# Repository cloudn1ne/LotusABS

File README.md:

# LotusABS

<table border=0>
<tr>
<td></td>
<td colspan=2></td>
</tr><tr>
<td></td>
<td></td>
<td></td>
</tr>
</table>

## What can you do with it ?

The software part is a pretty minimum implementation of the KWP2000 via K-LINE as used by the EBC430 EBC.
The supported Service IDs are:

Function | Usage
-------- | -----
StartCommunication | start a KWP2000 session
ReadECUIdentification | ECU details, nothing new here - same as listed in the Lotus Service Manual
ReadDataByLocalId | battery voltage, wheel speeds (not implemented, because my car is not moving atm)
ReadDiagnosticTroubleCodeByStatus | read DTC codes and status reasons
ClearDiagnosticInformationService | clear and DTCs
InputOutputControlByLocalId | control the valves, pump, relay

So with that you can establish communication with the ECU, get software/hardware versions, battery voltage (wheels speeds later on), read and clear DTCs, and most importantly
control the valves, pump and valve relay to aid with bleeding.

## How can i use it ?

You need to solder up the little ESP8266 based adapter (or put it on breadboard if you are adventurous. A proven PCB design and circuit is included in the ./pcb folder.
It was made with KiCAD (www.kicad.org)

## Whats the difference to existing KLINE/OBD Tools ?

Not much - i didnt have one, so i had to roll my own - the most notible difference is that the KLINE line has to be on PIN #12 of the OBD connector (usualy it would be Pin #7)
And you wont have a GUI to control stuff.

## Software
The project is based on PLATFORM.IO - download VS Code and install platform IO (https://platformio.org/) 

## Hardware
see KiCAD

### As usual that tool comes with no warranty, it might blow up your airbags (same KLINE) or set your car on fire. Good luck ;-)

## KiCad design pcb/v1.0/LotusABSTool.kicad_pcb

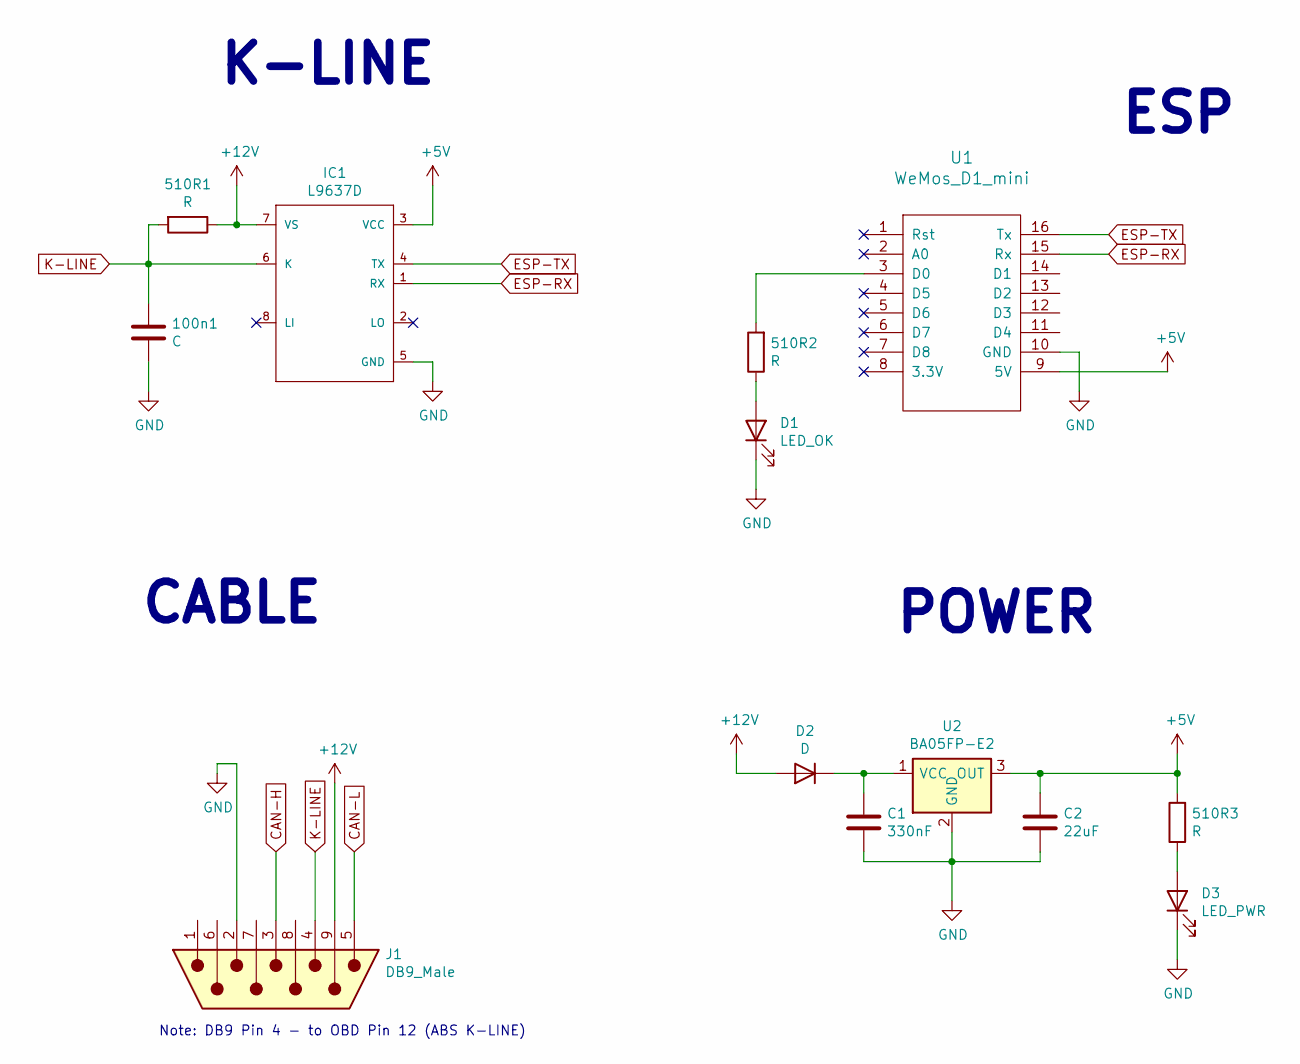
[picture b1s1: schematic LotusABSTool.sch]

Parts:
100n1: C; C_0805_2012Metric_Pad1.18x1.45mm_HandSolder
510R1, 510R2, 510R3: R; R_0805_2012Metric_Pad1.20x1.40mm_HandSolder
C1: 330nF; C_0805_2012Metric_Pad1.18x1.45mm_HandSolder
C2: 22uF; CP_Elec_10x10.5
D1: LED_OK; LED_0805_2012Metric_Pad1.15x1.40mm_HandSolder
D2: D; D_SMA-SMB_Universal_Handsoldering
D3: LED_PWR; LED_0805_2012Metric_Pad1.15x1.40mm_HandSolder
IC1: L9637D; SO-8_3.9x4.9mm_P1.27mm
J1: DB9_Male; DSUB-9_Male_Vertical_P2.77x2.84mm_MountingHoles
U1: WeMos_D1_mini; wemos-d1-mini-with-pin-header
U2: BA05FP-E2; TO-252-2

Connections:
+5V: 510R3.2, C2.1, IC1.3 (VCC), U1.9 (5V), U2.3 (OUT)
+12V: 510R1.1, D2.2 (A), IC1.7 (VS), J1.9
CAN-H: J1.3
CAN-L: J1.5
ESP-RX: IC1.1 (RX), U1.15 (Rx)
ESP-TX: IC1.4 (TX), U1.16 (Tx)
GND: 100n1.2, C1.2, C2.2, D1.1 (K), D3.1 (K), IC1.5 (GND), J1.2, U1.10 (GND), U2.2 (GND)
K-LINE: 100n1.1, 510R1.2, IC1.6 (K), J1.4
unnamed: 510R2.1, D1.2 (A)
unnamed: 510R2.2, U1.3 (D0)
unnamed: 510R3.1, D3.2 (A)
unnamed: C1.1, D2.1 (K), U2.1 (VCC)

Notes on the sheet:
K-LINE
ESP
POWER
CABLE
Note: DB9 Pin 4 - to OBD Pin 12 (ABS K-LINE)

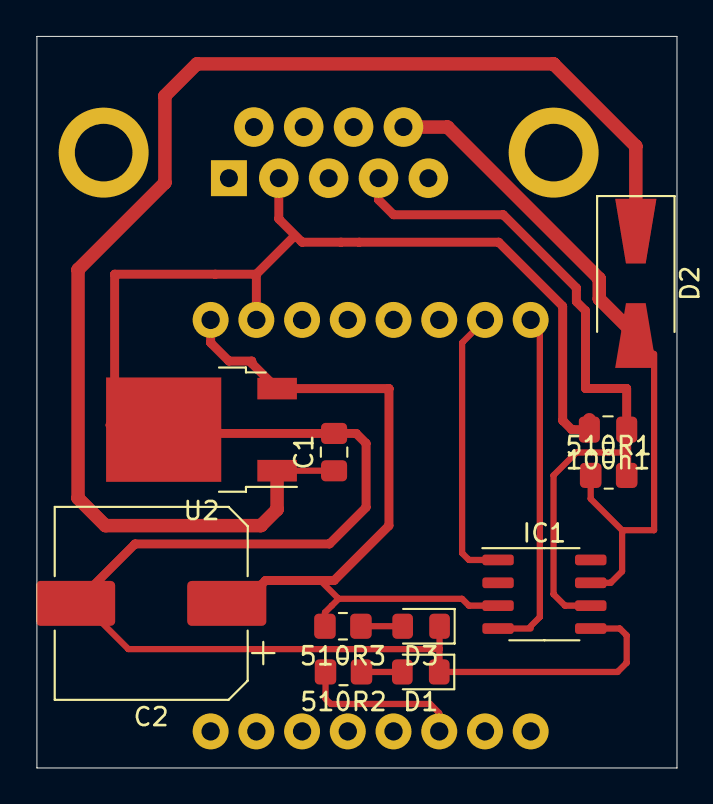
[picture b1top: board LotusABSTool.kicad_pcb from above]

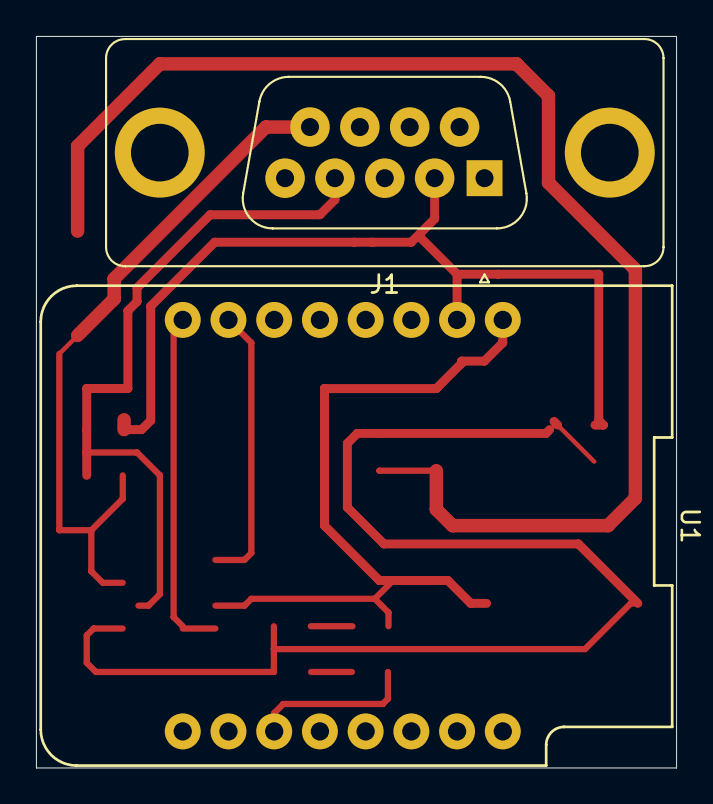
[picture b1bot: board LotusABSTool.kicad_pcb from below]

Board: 2 copper layers, 35.6 x 40.6 mm, 13 parts (2 on the bottom side), 10 nets.

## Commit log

2021-05-24 updated gitignore
2021-05-25 StartCommunication working in fastInit mode
2021-05-25 voltage reading also works
2021-05-26 fixed KWP2k handling when reconnecting, and implemented DTC list/clear functions
2021-05-28 DTC page and ECU Info page first version done, websocket support added
2021-05-28 valve control working
2021-05-28 added ErrorReporting to all pages
2021-05-30 prep for release
2021-05-30 added kicad v1.0
2021-05-30 upload
2021-05-30 blah
2021-05-30 added some pics
2021-05-30 resize img
2021-05-30 img tags
2021-05-30 table
2021-05-30 table2
